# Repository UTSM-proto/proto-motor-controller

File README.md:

# UTSM motor controller

RP2040 Pico firmware and StinkyController KiCad hardware.

On Windows, double-click **Launch Programmer.cmd** to edit the firmware configuration and build/program a connected Pico. The editor includes 40 settings plus the manual hall table, descriptions, sliders, numeric inputs, voltage conversion, profile import/export and a build log.

See [programmer setup and operation](programmer/README.md) for dependencies, firmware changes and testing. See [hardware files](hardware/StinkyController/README.md) for PCB revisions and manufacturing outputs. `blink.c` is the active firmware target; `temp.c` is a legacy copy and is not built.

The GUI generates an isolated configuration header for each build. The checked-in firmware defaults are in `firmware/controller_config.h`; `programmer/config.py` defines the editor schema and validation. Keep both synchronized when changing defaults.

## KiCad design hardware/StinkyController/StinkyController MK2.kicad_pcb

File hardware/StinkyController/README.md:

# StinkyController hardware

This directory contains the KiCad PCB projects and manufacturing outputs from
the supplied `StinkyController 0.5.zip` archive.

## Project revisions

- `StinkyController 0.5`
- `StinkyController 1`
- `StinkyController 1.1`
- `StinkyController MK2` (newest PCB and Gerber revision in the archive)

The `gerb*` directories and ZIP files contain the supplied manufacturing
outputs. Generated KiCad user preferences, caches, backups, and macOS metadata
are excluded from version control.

## Missing source

The supplied archive does not contain a `.kicad_sch` schematic file. The PCB
files retain component values, footprints, net names, and routed connectivity,
but the editable schematic source will need to be added separately if it still
exists.

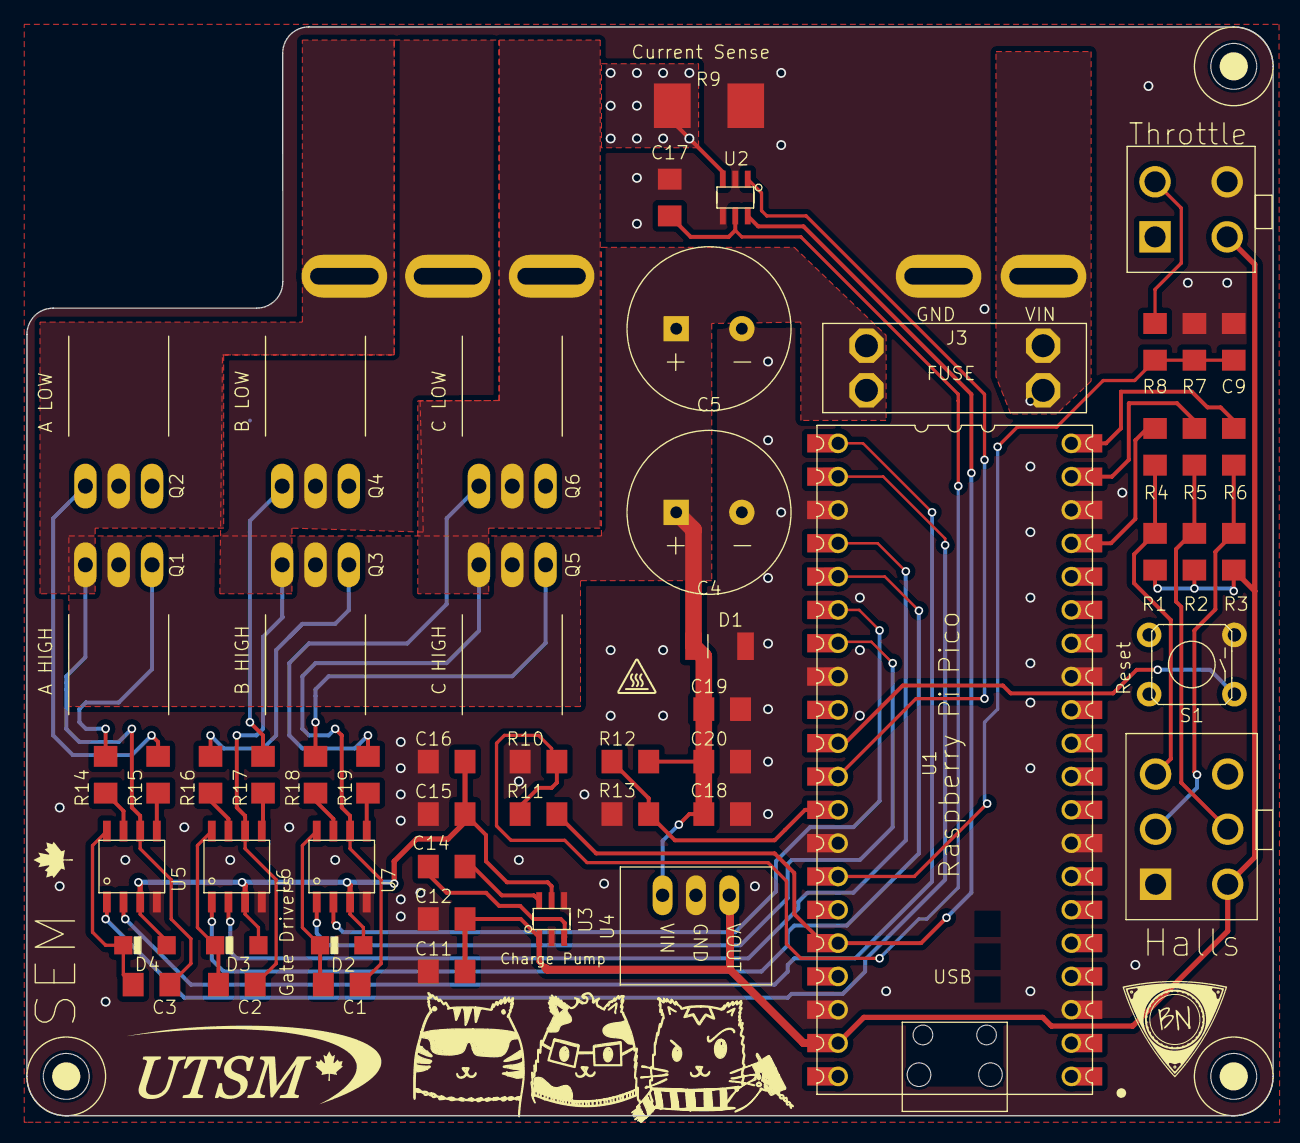
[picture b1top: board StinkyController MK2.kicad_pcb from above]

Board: 2 copper layers, 95.0 x 83.0 mm, 58 parts (0 on the bottom side), 46 nets.

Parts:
C1, C2, C3, C11, C12, C14, C15, C16, C17, C18, C19, C20: 1uF; 1206
C4, C5: 470uF; CPOL-RADIAL-5MM-10MM
C9: 22nF; 1206
D1: TVS; DO-214AC
D2, D3, D4: SOD-123
J1: HEADER4VALULOK; 4PINVALULOK
J2: HEADER6; 6PINVALULOK
J3: FUSE; AUTO_FUSE
Q1, Q2, Q3, Q4, Q5, Q6: TO-220-FLAT
R1, R2, R3, R4, R5, R6, R13: 2.2k; 1206
R7, R8, R10, R11, R12: 47k; 1206
R9: 0.0005; R2512
R14, R15, R16, R17, R18, R19: 22; 1206
S1: TACTILE_SWITCH_PTH_6.0MM
U1: PICO-PKG-NO_DEBUG
U2: INA181; SOT23-6
U3: TC1240A; SOT23-6
U4: K78U05; V78W_BACKWARDS
U5, U6, U7: DGD2304; SOIC8
U$10, U$11, U$12: SCREW; M3HOLE

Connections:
3.3V: R11.2, U1.36, U1.P$36, U2.6
5V: C11.1, C12.1, J1.2, J2.2, R1.2, R2.2, R3.2, U1.39, U1.P$39, U3.1, U4.OUT
10V: C15.1, C16.1, D2.+, D3.+, D4.+, U3.5, U5.3, U6.3, U7.3
COM_A: C3.2, Q1.3, Q2.2, U5.6
COM_B: C2.2, Q3.3, Q4.2, U6.6
COM_C: C1.2, Q5.3, Q6.2, U7.6
CTRL_AH: U1.21, U1.P$21, U5.2
CTRL_AL: U1.22, U1.P$22, U5.1
CTRL_BH: U1.24, U1.P$24, U6.2
CTRL_BL: U1.25, U1.P$25, U6.1
CTRL_CH: U1.26, U1.P$26, U7.2
CTRL_CL: U1.27, U1.P$27, U7.1
DRV_AH: R14.1, U5.7
DRV_AL: R15.1, U5.5
DRV_BH: R16.1, U6.7
DRV_BL: R17.1, U6.5
DRV_CH: R18.1, U7.7
DRV_CL: R19.1, U7.5
GND: C4.-, C5.-, C9.2, C11.2, C12.2, C15.2, C16.2, C17.2, C18.2, C19.2, C20.2, D1.A, J1.4, J2.1, R7.1, R9.1, R10.1, R13.1, S1.3, U1.3, U1.8, U1.13, U1.18, U1.23, U1.28, U1.33, U1.38, U1.P$3, U1.P$8, U1.P$13, U1.P$18, U1.P$23, U1.P$28, U1.P$33, U1.P$38, U2.2, U2.4, U3.2, U3.4, U4.GND, U5.4, U6.4, U7.4
HALL_A: R4.2, U1.17, U1.P$17
HALL_B: R5.2, U1.19, U1.P$19
HALL_C: R6.2, U1.20, U1.P$20
ISENSE: U1.31, U1.P$31, U2.1
unnamed: C2.1, D3.-, U6.8
unnamed: J2.3, R3.1, R6.1
unnamed: C3.1, D4.-, U5.8
unnamed: J2.4, R2.1, R5.1
unnamed: Q1.1, R14.2
unnamed: J2.5, R1.1, R4.1
unnamed: J1.3, R8.1
unnamed: C1.1, D2.-, U7.8
unnamed: S1.1, U1.30, U1.P$30
unnamed: C17.1, R10.2, R11.1, U2.5
unnamed: Q2.1, R15.2
unnamed: Q3.1, R16.2
unnamed: Q4.1, R17.2
unnamed: Q5.1, R18.2
unnamed: Q6.1, R19.2
unnamed: C14.1, U3.3
unnamed: C14.2, U3.6
SHUNT+: Q2.3, Q4.3, Q6.3, R9.2, U2.3
THROTTLE: C9.1, R7.2, R8.2, U1.34, U1.P$34
VBUS: U1.40, U1.P$40
VSENSE: R12.1, R13.2, U1.32, U1.P$32
V_PREFUSE: J3.1A, J3.1B
V_RAW: C4.+, C5.+, C18.1, C19.1, C20.1, D1.C, J3.2A, J3.2B, Q1.2, Q3.2, Q5.2, R12.2, U4.IN

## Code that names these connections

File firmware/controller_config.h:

// Generated configuration. Edit with the Windows programmer.
#pragma once
#define THROTTLE_LOW (540)
#define THROTTLE_HIGH (3300)
#define THROTTLE_INPUT_FULL_SCALE_V (5)
#define THROTTLE_SLEW_RATE (1)
#define CURRENT_CONTROL (0)
#define PHASE_MAX_CURRENT_MA (13000)
#define BATTERY_MAX_CURRENT_MA (13000)
#define CURRENT_CONTROL_LOOP_GAIN (700)
#define SYNCHRONOUS_SWITCHING (0)
#define SYNCHRONOUS_DELAY_CYCLES (16000)
#define IDENTIFY_HALLS_ON_BOOT (1)
#define IDENTIFY_HALLS_REVERSE (1)
#define HALL_IDENTIFY_DUTY_CYCLE (25)
#define HALL_IDENTIFY_SETTLE_MS (500)
#define HALL_IDENTIFY_STABLE_SAMPLES (20)
#define BOOT_DELAY_MS (2000)
#define HALL_OVERSAMPLE (8)
#define HALL_STABLE_CYCLES (2)
#define HALL_LOSS_TIMEOUT_CYCLES (16)
#define HALL_VALIDATE_TRANSITIONS (1)
#define CURRENT_SCALING (80.56640625)
#define VOLTAGE_SCALING (18.017578125)
#define ADC_BIAS_OVERSAMPLE (1000)
#define F_PWM (16000)
#define TELEMETRY_INTERVAL_MS (100)
#define PWM_FULL_ON_THRESHOLD (245)
#define PWM_COMPLEMENT_TOTAL (248)
#define LED_PIN (25)
#define FLAG_PIN (2)
#define AH_PIN (16)
#define AL_PIN (17)
#define BH_PIN (18)
#define BL_PIN (19)
#define CH_PIN (20)
#define CL_PIN (21)
#define HALL_1_PIN (13)
#define HALL_2_PIN (14)
#define HALL_3_PIN (15)
#define ISENSE_PIN (26)
#define VSENSE_PIN (27)
#define THROTTLE_PIN (28)
#define HALL_TABLE_INITIALIZER {255, 255, 255, 255, 255, 255, 255, 255}
#define DUTY_CYCLE_MAX 65535
// PWM slices and ADC channels are derived from GPIO assignments.
